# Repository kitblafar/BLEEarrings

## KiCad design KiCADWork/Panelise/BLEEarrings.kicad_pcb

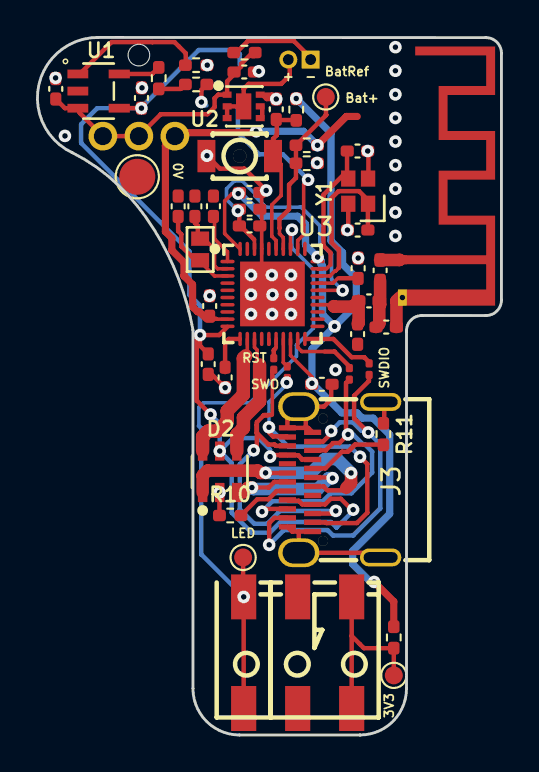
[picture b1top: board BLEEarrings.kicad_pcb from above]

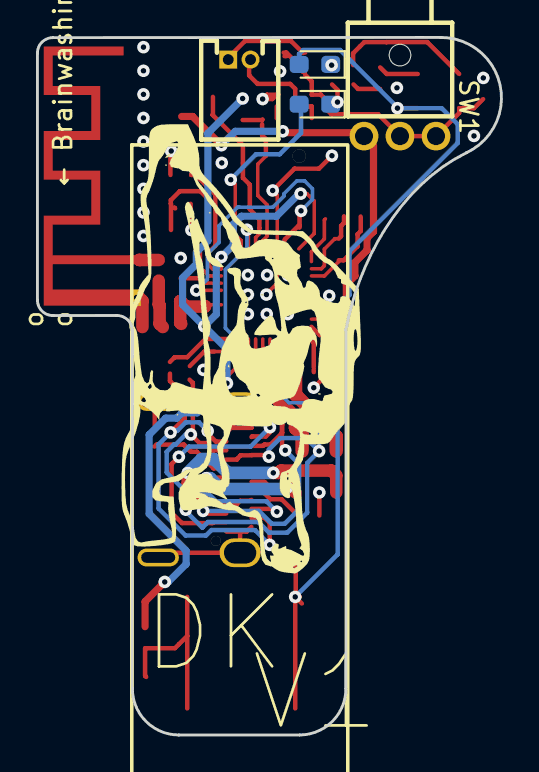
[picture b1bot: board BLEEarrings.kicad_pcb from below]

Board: 2 copper layers, 25.8 x 38.8 mm, 54 parts (4 on the bottom side), 41 nets.

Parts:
ANT1: Texas_SWRA117D_2.4GHz_Left
BT1: Battery; CONN-TH_530480210
C1, C7: 1u; C_0402_1005Metric_Pad0.74x0.62mm_HandSolder
C2, C6, C14, C18: 100n; C_0402_1005Metric_Pad0.74x0.62mm_HandSolder
C3, C4: 12p; C_0402_1005Metric_Pad0.74x0.62mm_HandSolder
C5: 1.2p; C_0402_1005Metric_Pad0.74x0.62mm_HandSolder
C8: 1p; C_0402_1005Metric_Pad0.74x0.62mm_HandSolder
C9, C10, C12: 4.7u; C_0402_1005Metric_Pad0.74x0.62mm_HandSolder
C11: 100p; C_0402_1005Metric_Pad0.74x0.62mm_HandSolder
C13, C19: 10u; C_0402_1005Metric_Pad0.74x0.62mm_HandSolder
C15, C16: 8p; C_0402_1005Metric_Pad0.74x0.62mm_HandSolder
C17: NC; C_0402_1005Metric_Pad0.74x0.62mm_HandSolder
D1: RED LED; LED_0603_1608Metric_Pad1.05x0.95mm_HandSolder
D2: USBLC6-2SC6_C2687116; SOT-23-6_L2.9-W1.6-P0.95-LS2.8-BL
D4: BLUE LED; LED_0603_1608Metric_Pad1.05x0.95mm_HandSolder
J1: Screw_Terminal_01x01; CONN-SMD_custom1
J2: Screw_Terminal_01x02; CONN-SMD_2059-302
J3: USB_C_Receptacle; TYPE-C-SMD_C9900025773
L1: 4.7n; L_0402_1005Metric_Pad0.77x0.64mm_HandSolder
L2: 2.2n; L_0402_1005Metric_Pad0.77x0.64mm_HandSolder
R1, R2: 2k; R_0402_1005Metric_Pad0.72x0.64mm_HandSolder
R3: 100; R_0402_1005Metric_Pad0.72x0.64mm_HandSolder
R4: 4k99; R_0402_1005Metric_Pad0.72x0.64mm_HandSolder
R5, R6, R7, R8: NF; R_0201_0603Metric
R9: 470; R_0402_1005Metric_Pad0.72x0.64mm_HandSolder
R10, R11: 5k1; R_0402_1005Metric_Pad0.72x0.64mm_HandSolder
R12: 220; R_0402_1005Metric_Pad0.72x0.64mm_HandSolder
R13: 100k; R_0402_1005Metric_Pad0.72x0.64mm_HandSolder
R14: 33k; R_0402_1005Metric_Pad0.72x0.64mm_HandSolder
SW1: TK-6580B-1; SW-TH_TK-6580B-1
SW2: SW_DIP_x01; KEY-SMD_L3.0-W2.5-LS4.0
TP9, TP10, TP11: TestPoint; TestPoint_Pad_D1.0mm
TP16: TestPoint; TestPoint_Pad_D2.0mm
U1: MCP73831T-2ACI/OT; SOT-23-5_L3.0-W1.7-P0.95-LS2.8-BL
U2: XB6096I2SV; WDFN-6_L2.0-W2.0-P0.65-BL-EP
U3: NRF52833-QDAA-R7; QFN-40_L5.0-W5.0-P0.40-TL-EP3.6
Y1: XL7EL89CKI-111YLC-32M; CRYSTAL-SMD_4P-L2.0-W1.6-BL
Y2: X161032768KLD2SI; CRYSTAL-SMD_L1.6-W1.0

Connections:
+3V3: C1.2, C6.1, R2.2, R9.2, U3.18 (VDD), U3.30 (VDD), U3.40 (VDD)
+BATT: C12.2, R13.2, SW1.3, U3.9 (VDDH)
/DSP/VBUS: C10.2, C19.1, D1.2 (A), D2.5 (VBUS), J3.A4 (VBUS), U1.4 (VDD), U3.10 (VBUS)
/DSP/nReset: J3.A10 (RX2-), J3.B10 (RX1-), R5.1
/Power/VBAT: C13.1, C18.1, R3.2, SW1.1, SW1.2, U1.3 (VBAT), U2.1 (VDD)
BatRef: R13.1, R14.2, TP9.1, U3.34 (P0.29_AIN5)
D+: D2.4 (I/O2), U3.13 (D+)
D-: D2.6 (I/O1), U3.12 (D-)
DEC6: C7.1, C17.1, U3.26 (DEC6), U3.38 (DEC4)
GND: ANT1.2 (GND), C1.1, C2.1, C3.1, C4.1, C5.2, C6.2, C7.2, C8.2, C9.1, C10.1, C11.2, C12.1, C13.2, C14.1, C15.1, C16.1, C17.2, C18.2, C19.2, D2.2 (GND), J2.2, J3.A1 (GND), J3.S1 (SHIELD), R4.2, R10.1, R11.1, R12.1, R14.1, SW2.2, TP16.1, U1.2 (VSS), U2.4 (VM), U2.5 (VM), U2.6 (VM), U3.37 (VSS), U3.41 (VSS), Y1.2, Y1.3
LED_A: D4.2 (A), U3.32 (P0.02_AIN0)
NEO_LED: J1.1, TP10.1, U3.33 (P0.28_AIN4)
unnamed: ANT1.1 (FP), L2.2
unnamed: BT1.1 (+), R3.1
unnamed: BT1.2 (-), U2.2 (GND), U2.3 (GND), U2.7 (EP)
unnamed: C5.1, L1.2, L2.1
unnamed: D1.1 (K), R1.1
unnamed: D2.1 (I/O1), J3.A7 (D-), J3.B7 (D-)
unnamed: D2.3 (I/O2), J3.A6 (D+), J3.B6 (D+)
unnamed: D4.1 (K), R12.2
unnamed: J2.1, R9.1, TP11.1
unnamed: J3.A5 (CC1), R10.2
unnamed: J3.B5 (CC2), R11.2
unnamed: R4.1, U1.5 (PROG)
unnamed: R1.2, U1.1 (STAT)
unnamed: C8.1, L1.1, U3.24 (ANT)
unnamed: C2.2, U3.1 (DEC1)
unnamed: C11.1, U3.27 (DEC3)
unnamed: C9.2, U3.11 (DECUSB)
unnamed: C16.2, U3.2 (P0.00_XL1), Y2.2
unnamed: C15.2, U3.3 (P0.01_XL2), Y2.1
unnamed: R5.2, U3.16 (P0.18_nRESET)
unnamed: R6.1, U3.17 (P0.20)
unnamed: R7.1, U3.20 (SWDCLK)
unnamed: R8.2, U3.19 (SWDIO)
unnamed: C3.2, U3.28 (XC1), Y1.1
unnamed: C4.2, U3.29 (XC2), Y1.4
Pair: C14.2, R2.1, SW2.1, U3.35 (P0.30_AIN6)
SWDCLK_L: J3.A3 (TX1-), J3.B3 (TX2-), R8.1
SWDIO_L: J3.A2 (TX1+), J3.B2 (TX2+), R7.2
SWO_L: J3.A11 (RX2+), J3.B11 (RX1+), R6.2
